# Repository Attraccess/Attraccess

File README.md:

# Attraccess

Attraccess manages machine access and resource usage for industry, R&D and universities. It checks operator permissions and safety briefings, connects machines through PLCs and automation flows, and records usage for reporting and maintenance.

Attraccess runs on your own infrastructure and is **source-available** under the [modified Prosperity Public License 3.0](LICENSE.md). Commercial use requires a license after a 30-day evaluation; qualifying non-commercial use is free under the license terms.

## Features

- Resource Management
  - Track resource status, usage, and maintenance
  - Image support for resources with automatic resizing and caching
  - Operator permissions and documented safety briefings
  - Preventive maintenance scheduling
  - Usage tracking, project attribution and CSV reporting
- Machine Integration
  - Badge access through Attractap readers
  - WAGO PLC integration and automation via MQTT and HTTP
  - Workstation access through Attraccess Companion
- IT & Operations
  - Single sign-on via OIDC and SAML
  - Role-based access control and audit logging
  - On-premises deployment with Prometheus and Grafana monitoring

## Everything below is meant for developers

If you are looking for user documentation, take a look at https://docs.attraccess.org

## Developer Setup

Routine API/frontend work needs:

| Dependency  | Purpose                                              |
| ----------- | ---------------------------------------------------- |
| **Docker**  | `pnpm services` – PostgreSQL, mailpit, authentik, etc. |
| **Node.js** | Exact version pinned in `.nvmrc`                     |
| **pnpm**    | Exact version pinned in `package.json`               |

**Quick setup:**

```bash
./scripts/setup-dev-dependencies.sh
```

This checks the pinned Node and pnpm versions, installs missing host tools, and
sets up the workspace (dependencies, `.env`, submodules, the PostgreSQL database and its migrations).
PostgreSQL is the only supported database. Every checkout gets its own database
`attraccess_<folder>` inside the shared development PostgreSQL
(`pnpm services up postgres`, host port `POSTGRES_PORT`, default 5432); the
bootstrap starts that service when nothing answers, creates the database and writes
`DATABASE_URL` into `.env` (`scripts/setup-dev-database.mjs`).
Host installation is in `scripts/setup-host-dependencies.sh`; workspace setup is
in `scripts/setup-workspace.sh`. To repeat workspace setup without installing
global tools, run `./scripts/setup-dev-dependencies.sh --workspace-only`.
Docker (or any PostgreSQL reachable through `DATABASE_URL` / `DEV_POSTGRES_URL`) is needed for the
development database; services and container tests need a running Docker daemon and the
`docker compose` plugin. Install **Docker** manually if missing:

- **Docker:** `curl -fsSL https://get.docker.com | sh` then `sudo usermod -aG docker $USER` (log out/in)

For Attractap firmware work, also install the project-local ESP-IDF toolchain:

```bash
INSTALL_ESP_IDF=true ./scripts/setup-dev-dependencies.sh --workspace-only
```

## Installation

1. Clone the repository
2. Install dependencies:
   ```bash
   pnpm install
   ```
3. Set up environment variables and the development database (creates `attraccess_<folder>`, writes `DATABASE_URL`):
   ```bash
   cp .env.example .env
   pnpm services up postgres
   node scripts/setup-dev-database.mjs
   ```
4. Run database migrations:
   ```bash
   pnpm nx run api:migrations-run
   ```

## Development

Tooling tests run as an ordinary Nx target, independently of coverage reporting:

```bash
pnpm test:tooling
pnpm nx run api:test-scripts
```

Core CI discovers these targets automatically. `api:test` also runs the seeding
regressions. `pnpm seed:dev -- --demo` creates a local administrator and demo
resources after migrations. Seeding and migrations read `.env`; process variables
take precedence. Both use `DATABASE_URL`; seeding a database on a host other than
localhost requires `--allow-external-db`. API and script tests that need PostgreSQL read
`TEST_DATABASE_URL` (an admin connection such as
`postgres://attraccess:attraccess@127.0.0.1:5432/postgres`) and create one database per test.

Repository checks and generators are available through Nx:

```bash
pnpm lint:files                           # always checks current files
pnpm lint:files --staged                  # always checks the Git index
pnpm nx run @attraccess/source:check-balena-compose
pnpm nx run @attraccess/source:check-brand-assets
pnpm nx run @attraccess/source:generate-brand-assets
```

Validation targets can cache their results. Bootstrap, seeding, migrations,
service management and asset generation always execute.

Start the API and frontend in development mode (HMR), with automatic port resolution:

```bash
pnpm serve
```

By default, startup does not build or copy kiosk (Companion) installers or
Attractap firmware. Build and bundle either set of assets before launching:

```bash
pnpm serve --with-kiosk                  # Companion installers for this host
pnpm serve --with-attractap              # Active Attractap firmware variants
pnpm serve --with-kiosk --with-attractap # Both
```

`--with-companion` is an alias for `--with-kiosk`. These flags also work with
`--only=api`; frontend-only startup cannot prepare API assets. Requested builds
must succeed before the servers launch. Firmware builds require ESP-IDF:
`INSTALL_ESP_IDF=true ./scripts/setup-dev-dependencies.sh`.

CI always tests the deliverables and builds all Companion platforms and active
firmware variants. Docker and Balena consume the same uploaded artifacts;
missing installers or firmware fail the image build.

The launcher probes for free ports and prints them at startup. Defaults:

- API: 3000 (searches 3000–3099)
- Frontend: 4200 (searches 4200–4299)
- Vite preview: 4300 (searches 4300–4399)

Run only one service:

```bash
pnpm serve --only=api
pnpm serve --only=frontend
```

Use the nx interactive terminal UI instead of streamed output (default is streamed, which is agent/CI friendly):

```bash
pnpm serve --tui
```

Pin a specific port (fails loudly if busy):

```bash
PORT=3010 pnpm serve              # API on 3010
VITE_PORT=4250 pnpm serve         # Frontend on 4250
```

The frontend dev proxy automatically targets whichever port the API resolved to (via `VITE_API_PROXY_TARGET`).

The resolved ports are also written to `.dev-serve-ports.json` at the repo root (gitignored, deleted on exit), so you can look them up without reading the banner:

```bash
cat .dev-serve-ports.json
# { "pid": 12345, "api": {...}, "frontend": {...}, "preview": {...} }
```

## API Documentation

Swagger documentation is available at `/api` when the server is running.

## Licensing & Activation

Attraccess includes license verification. Enter your key in the setup wizard or under **Settings → Application Settings**; Attraccess does not read it from environment variables.

- Commercial users: Use the license key you received after purchasing a license.
- Non-profit organizations: You can use Attraccess for free by entering the following special key:

```
I AM USING THIS SOFTWARE ONLY FOR NON-PROFIT AND COMPLY TO ALL TERMS OF THE LICENSE.md at https://github.com/Attraccess/Attraccess/blob/main/LICENSE.md
```

Licensed features require a valid configured key.

Plugins fall under the core license unless they ship their own `LICENSE.md`. The WAGO and Reservations plugins have their own commercial license and need a paid license module (`wago`, `reservations`); the non-profit key does not unlock them.

## Contributing

Please see [CONTRIBUTING.md](CONTRIBUTING.md) for details on our code of conduct and the process for submitting pull requests.

## Lizenz

Dieses Projekt ist **source-available** und steht unter einer modifizierten Version der [Prosperity Public License v3.0](./LICENSE.md).

### ✅ Erlaubt:

- Nutzung, Veränderung und Weitergabe für **Privatpersonen** und **gemeinnützige Organisationen**
- 30-tägige Testnutzung für **kommerzielle Nutzer**

### ❌ Nicht erlaubt:

- Kommerzielle Nutzung über 30 Tage hinaus **ohne kommerzielle Lizenz**
- Verwendung oder Verbreitung von Forks für kommerzielle Zwecke ohne Genehmigung
- Umlizensierung oder Änderung der Lizenzbedingungen

### 🛡️ Schutz vor Fork-Missbrauch

Alle Forks und abgeleiteten Projekte unterliegen denselben Lizenzbedingungen. Kommerzielle Nutzung ist auch in Forks **nicht erlaubt**, es sei denn, es liegt eine gültige Lizenz des ursprünglichen Autors vor.

### 🔌 Plugins

Plugins stehen unter der Lizenz des Kerns, sofern sie keine eigene `LICENSE.md` mitbringen. Die Plugins WAGO und Reservierungen haben eine eigene kommerzielle Lizenz und brauchen ein bezahltes Lizenzmodul (`wago`, `reservations`); der Schlüssel für gemeinnützige Nutzung schaltet sie nicht frei.

### 🔍 MIT-lizenzierte Bestandteile

Dieses Projekt basiert teilweise auf einem MIT-lizenzierten Projekt. Diese Komponenten bleiben unter der MIT-Lizenz verfügbar. Details siehe [LICENSE-fabinfra.md](./LICENSE-fabinfra.md).

---

**Für kommerzielle Nutzung oder Lizenzanfragen:**  
Bitte kontaktiere [contact@attraccess.org](mailto:contact@attraccess.org).

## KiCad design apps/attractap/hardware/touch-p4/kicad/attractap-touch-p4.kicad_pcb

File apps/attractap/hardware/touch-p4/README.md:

# Attractap Touch P4 board

KiCad project, generator, simulations and 3D-printable case of the Attractap Touch P4 reader board
(Nx project `attractap-touch-p4-pcb`). The documentation is in the docs under Hardware:
[docs/en/hardware/touch-p4/overview.md](../../../../docs/en/hardware/touch-p4/overview.md).

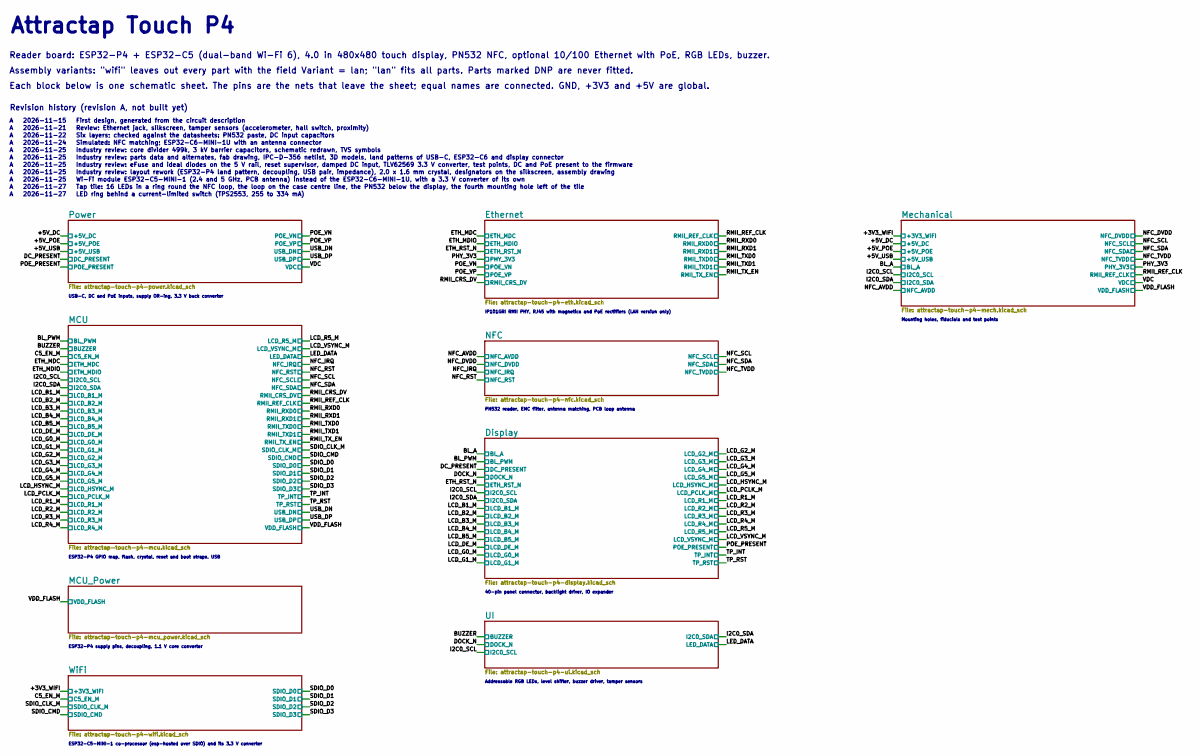
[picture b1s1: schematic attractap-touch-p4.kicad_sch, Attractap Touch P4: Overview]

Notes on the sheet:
USB-C, DC and PoE inputs, supply OR-ing, 3.3 V buck converter
ESP32-P4 GPIO map, flash, crystal, reset and boot straps, USB
ESP32-P4 supply pins, decoupling, 1.1 V core converter
ESP32-C5-MINI-1 co-processor (esp-hosted over SDIO) and its 3.3 V converter
IP101GRI RMII PHY, RJ45 with magnetics and PoE rectifiers (LAN version only)
PN532 reader, EMC filter, antenna matching, PCB loop antenna
40-pin panel connector, backlight driver, IO expander
Addressable RGB LEDs, level shifter, buzzer driver, tamper sensors
Mounting holes, fiducials and test points
Attractap Touch P4
Reader board: ESP32-P4 + ESP32-C5 (dual-band Wi-Fi 6), 4.0 in 480x480 touch display, PN532 NFC, optional 10/100 Ethernet with PoE, RGB LEDs, buzzer.
Assembly variants: "wifi" leaves out every part with the field Variant = lan; "lan" fits all parts. Parts marked DNP are never fitted.
Each block below is one schematic sheet. The pins are the nets that leave the sheet; equal names are connected. GND, +3V3 and +5V are global.
Revision history (revision A, not built yet)
A 2026-11-15 First design, generated from the circuit description
A 2026-11-21 Review: Ethernet jack, silkscreen, tamper sensors (accelerometer, hall switch, proximity)
A 2026-11-22 Six layers; checked against the datasheets: PN532 paste, DC input capacitors
A 2026-11-24 Simulated: NFC matching; ESP32-C6-MINI-1U with an antenna connector
A 2026-11-25 Industry review: core divider 499k, 3 kV barrier capacitors, schematic redrawn, TVS symbols
A 2026-11-25 Industry review: parts data and alternates, fab drawing, IPC-D-356 netlist, 3D models, land patterns of USB-C, ESP32-C6 and display connector
A 2026-11-25 Industry review: eFuse and ideal diodes on the 5 V rail, reset supervisor, damped DC input, TLV62569 3.3 V converter, test points, DC and PoE present to the firmware
A 2026-11-25 Industry review: layout rework (ESP32-P4 land pattern, decoupling, USB pair, impedance), 2.0 x 1.6 mm crystal, designators on the silkscreen, assembly drawing
A 2026-11-25 Wi-Fi module ESP32-C5-MINI-1 (2.4 and 5 GHz, PCB antenna) instead of the ESP32-C6-MINI-1U, with a 3.3 V converter of its own
A 2026-11-27 Tap tile: 16 LEDs in a ring round the NFC loop, the loop on the case centre line, the PN532 below the display, the fourth mounting hole left of the tile
A 2026-11-27 LED ring behind a current-limited switch (TPS2553, 255 to 334 mA)

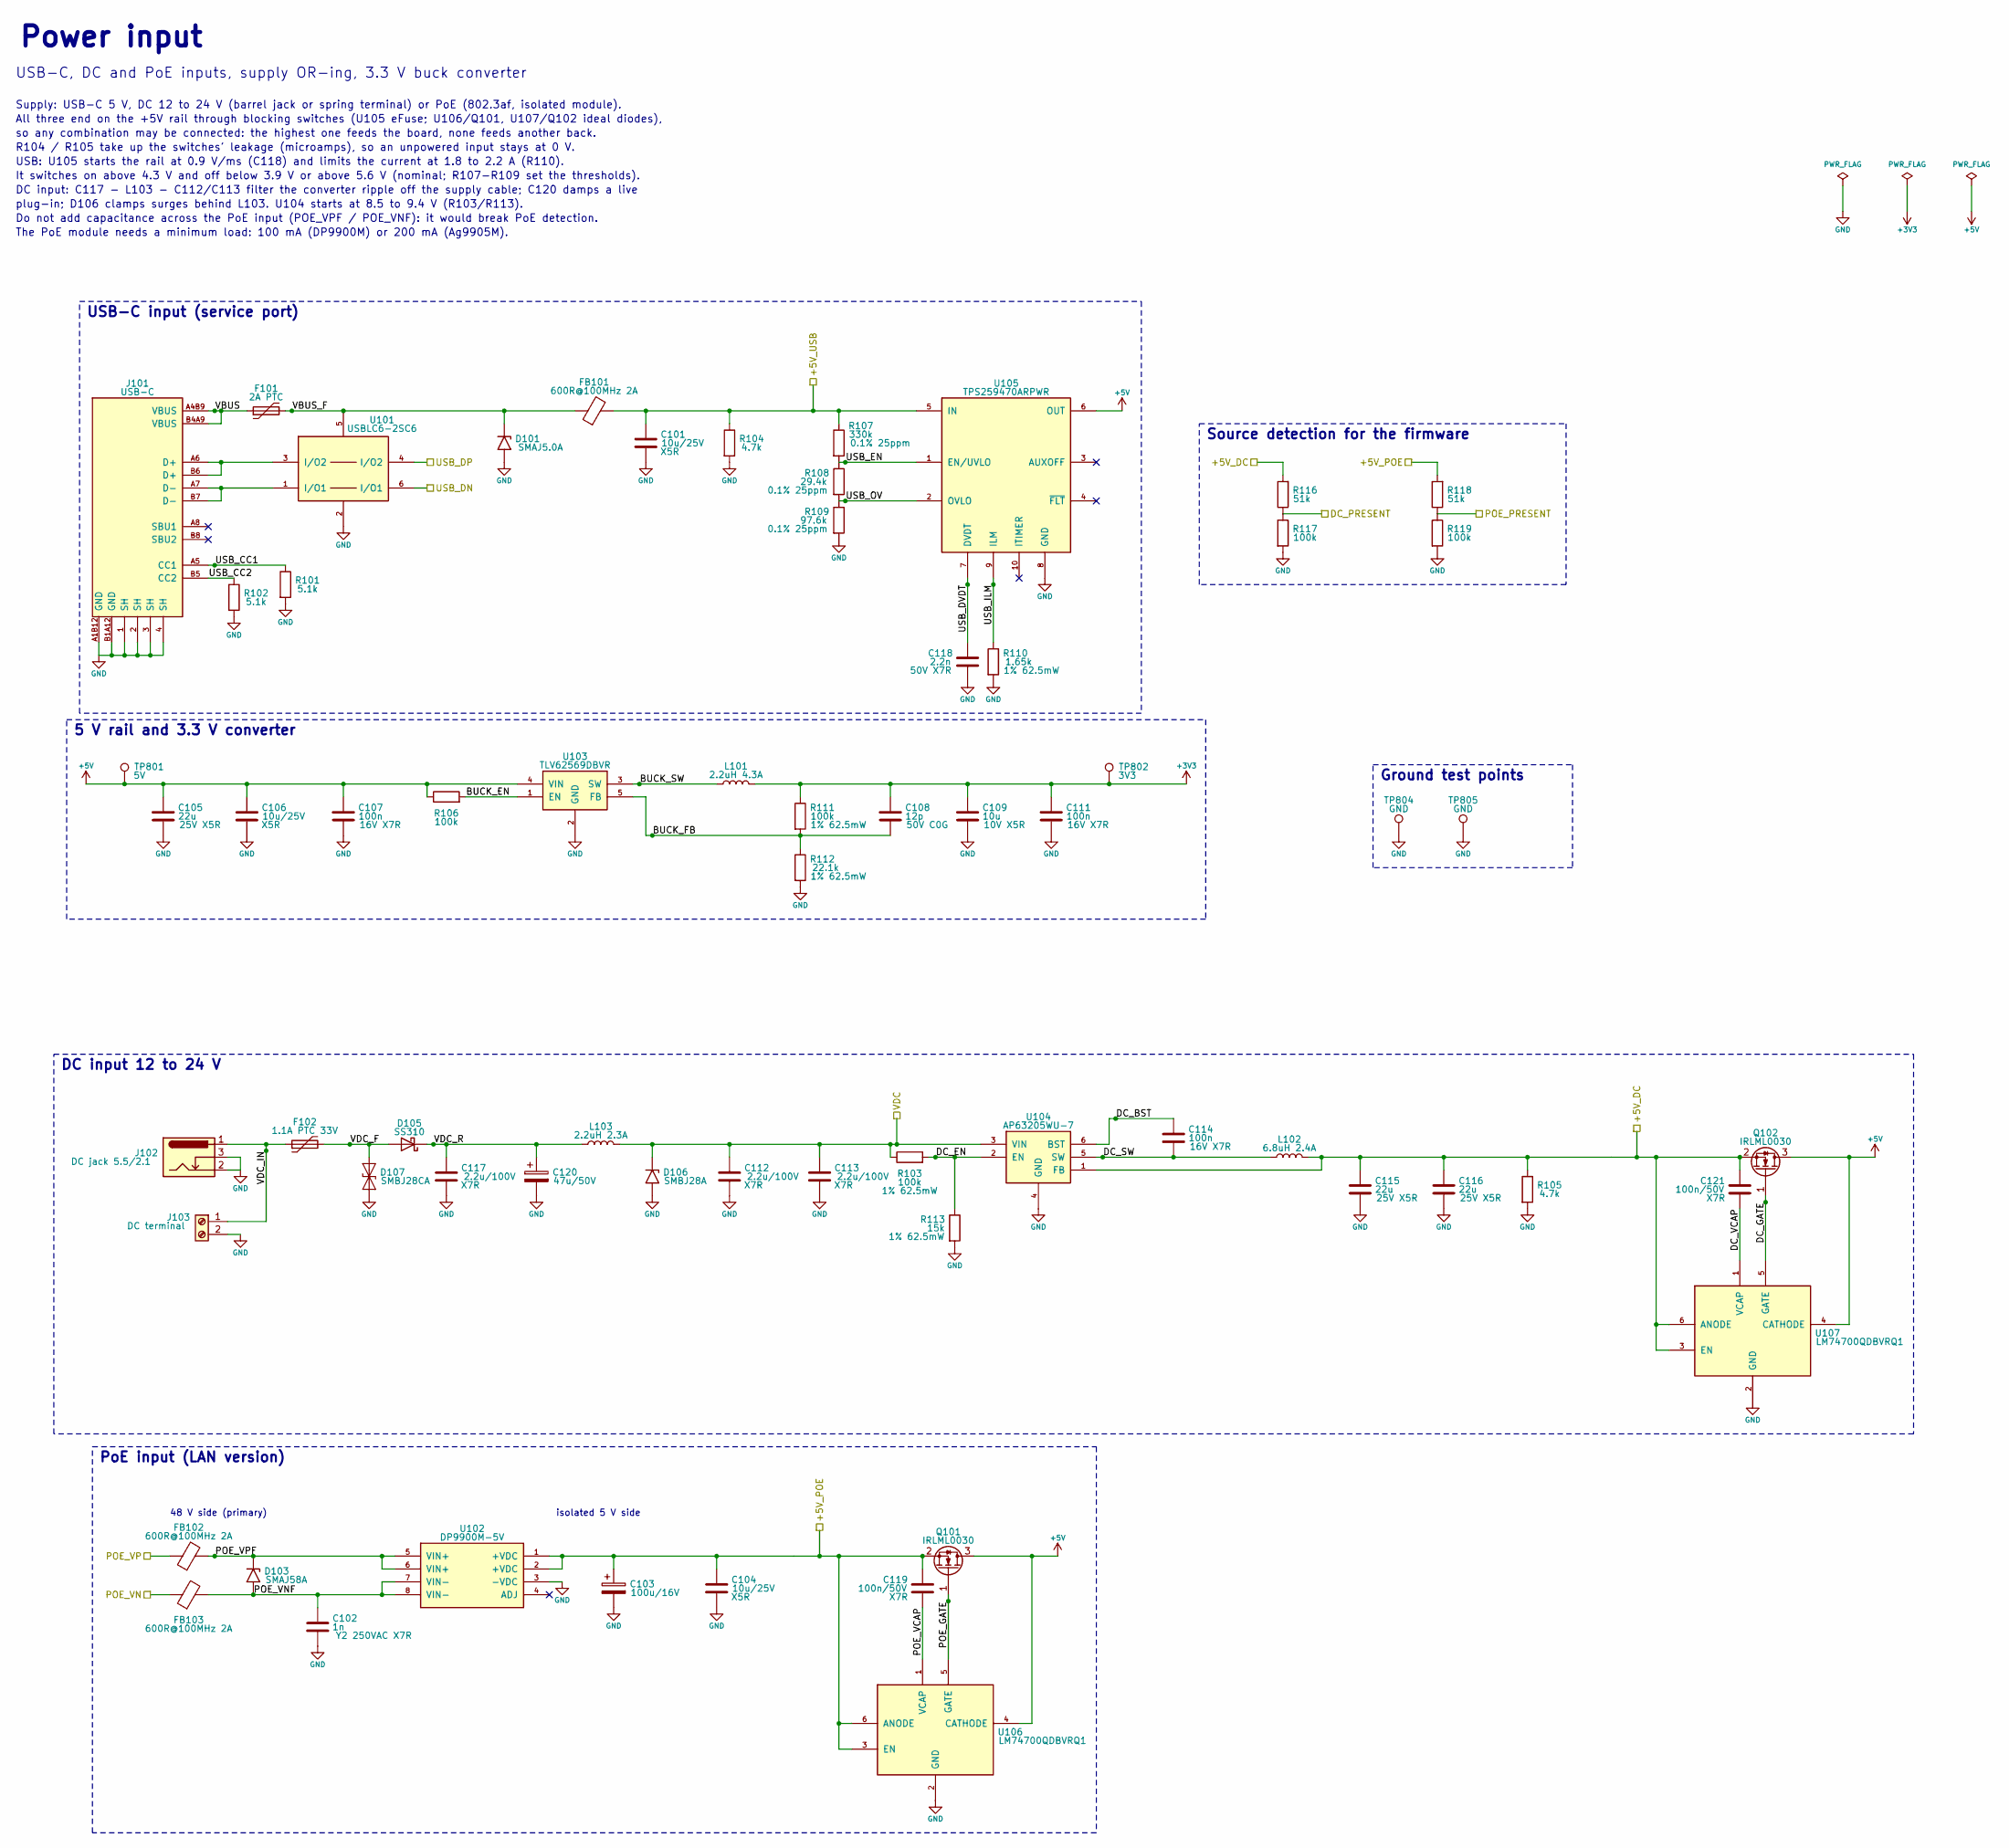
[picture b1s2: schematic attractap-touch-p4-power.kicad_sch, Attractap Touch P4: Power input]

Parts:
C101, C104, C106: 10u/25V; C_0805_2012Metric; Rating X5R; MPN CL21A106KAYNNNE; LCSC C15850
C102: 1n; C_2211_5728Metric_Y2; Rating Y2 250VAC X7R; MPN GA352QR7GF102KW01L; LCSC C91599
C103: 100u/16V; CP_Elec_6.3x5.4; MPN FVH016ADA101M0654; LCSC C7469977
C105, C115, C116: 22u; C_0805_2012Metric; Rating 25V X5R; MPN CL21A226MAQNNNE; LCSC C45783
C107, C111, C114: 100n; C_0402_1005Metric; Rating 16V X7R; MPN CL05B104KO5NNNC; LCSC C1525
C108: 12p; C_0402_1005Metric; Rating 50V C0G; MPN 0402CG120J500NT; LCSC C1547
C109: 10u; C_0603_1608Metric; Rating 10V X5R; MPN CL10A106KP8NNNC; LCSC C19702
C112, C113, C117: 2.2u/100V; C_1206_3216Metric; Rating X7R; MPN CL31B225KCHSNNE; LCSC C170101
C118: 2.2n; C_0402_1005Metric; Rating 50V X7R; MPN CL05B222KB5NNNC; LCSC C84703
C119, C121: 100n/50V; C_0402_1005Metric; Rating X7R; MPN CL05B104KB54PNC; LCSC C307331
C120: 47u/50V; CP_Elec_6.3x7.7; MPN UCD1H470MCL1GS; LCSC C251040
D101: SMAJ5.0A; SMA_L4.3-W2.6-LS5.2-RD; MPN SMAJ5.0A; LCSC C19077523
D103: SMAJ58A; SMA_L4.3-W2.6-LS5.2-RD; MPN SMAJ58A; LCSC C19077554
D105: SS310; SMA_L4.3-W2.6-LS5.2-RD; MPN SS310; LCSC C7420364
D106: SMBJ28A; D_SMB; MPN SMBJ28A; LCSC C178227
D107: SMBJ28CA; D_SMB; MPN SMBJ28CA; LCSC C151259
F101: 2A PTC; F1812; MPN MF-MSMF200L-2; LCSC C89650
F102: 1.1A PTC 33V; F1812; MPN SMD1812P110TF/33; LCSC C21000
FB101, FB102, FB103: 600R@100MHz 2A; L0805; MPN MPZ2012S601AT000; LCSC C21519
J101: USB-C; USB-C_SMD-TYPE-C-31-M-12_1; MPN TYPE-C-31-M-12; LCSC C165948
J102: DC jack 5.5/2.1; DC-IN-TH_PJ-002A; MPN PJ-002A; LCSC C3096082
J103: DC terminal; CONN-TH_4P-P3.5-2601-3102; MPN 250-202; LCSC C2765061
L101: 2.2uH 4.3A; IND-SMD_L4.0-W4.0; MPN WPN4020H2R2MT; LCSC C98361
L102: 6.8uH 2.4A; IND-SMD_L4.0-W4.0; MPN CKCSA4020-6.8uH/M; LCSC C5291940
L103: 2.2uH 2.3A; IND-SMD_L2.5-W2.0_CKCSA252012; MPN CKCSA252012-2.2uH/M; LCSC C354540
Q101, Q102: IRLML0030; SOT-23; MPN IRLML0030TRPBF; LCSC C67272
R101, R102: 5.1k; R_0402_1005Metric; Rating 1% 62.5mW; MPN 0402WGF5101TCE; LCSC C25905
R103, R106, R111, R117, R119: 100k; R_0402_1005Metric; Rating 1% 62.5mW; MPN 0402WGF1003TCE; LCSC C25741
R104, R105: 4.7k; R_0402_1005Metric; Rating 1% 62.5mW; MPN 0402WGF4701TCE; LCSC C25900
R107: 330k; R_0603_1608Metric; Rating 0.1% 25ppm; MPN RT0603BRD07330KL; LCSC C861327
R108: 29.4k; R_0402_1005Metric; Rating 0.1% 25ppm; MPN RT0402BRD0729K4L; LCSC C852690
R109: 97.6k; R_0402_1005Metric; Rating 0.1% 25ppm; MPN RT0402BRD0797K6L; LCSC C852964
R110: 1.65k; R_0402_1005Metric; Rating 1% 62.5mW; MPN 0402WGF1651TCE; LCSC C25869
R112: 22.1k; R_0402_1005Metric; Rating 1% 62.5mW; MPN 0402WGF2212TCE; LCSC C43473
R113: 15k; R_0402_1005Metric; Rating 1% 62.5mW; MPN 0402WGF1502TCE; LCSC C25756
R116, R118: 51k; R_0402_1005Metric; Rating 1% 62.5mW; MPN 0402WGF5102TCE; LCSC C25794
TP801: 5V; TestPoint_Pad_D1.5mm
TP802: 3V3; TestPoint_Pad_D1.5mm
TP804, TP805: GND; TestPoint_Pad_D1.5mm
U101: USBLC6-2SC6; SOT-23-6_L2.9-W1.6-P0.95-LS2.8-BL; MPN USBLC6-2SC6; LCSC C7519
U102: DP9900M-5V; PWRM-SMD_DP9900M-5V; MPN DP9900M-5V; LCSC C5380106
U103: TLV62569DBVR; SOT-23-5_L3.0-W1.7-P0.95-LS2.8-BR; MPN TLV62569DBVR; LCSC C141836
U104: AP63205WU-7; TSOT-26_L2.9-W1.6-P0.95-LS2.8-BL; MPN AP63205WU-7; LCSC C2071056
U105: TPS259470ARPWR; VQFN-10_L2.0-W2.0-P0.45-TL; MPN TPS259470ARPWR; LCSC C3662799
U106, U107: LM74700QDBVRQ1; SOT-23-6_L2.9-W1.6-P0.95-LS2.8-BL; MPN LM74700QDBVRQ1; LCSC C2941042

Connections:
+3V3: C108.1, C109.1, C111.1, L101.2, R111.1, TP802.1; also elsewhere on the board
+5V: C105.1, C106.1, C107.1, Q101.3 (D), Q102.3 (D), R106.1, TP801.1, U103.4 (VIN), U105.6 (OUT), U106.4 (CATHODE), U107.4 (CATHODE); also elsewhere on the board
/+5V_DC: C115.1, C116.1, C121.1, L102.2, Q102.2 (S), R105.1, R116.2, U104.1 (FB), U107.3 (EN), U107.6 (ANODE); also elsewhere on the board
/+5V_POE: C103.1, C104.1, C119.1, Q101.2 (S), R118.2, U102.1 (+VDC), U102.2 (+VDC), U106.3 (EN), U106.6 (ANODE); also elsewhere on the board
/+5V_USB: C101.1, FB101.2, R104.1, R107.1, U105.5 (IN); also elsewhere on the board
/DC_PRESENT: R116.1, R117.1; also elsewhere on the board
/POE_PRESENT: R118.1, R119.1; also elsewhere on the board
/POE_VN: FB103.1; also elsewhere on the board
/POE_VP: FB102.1; also elsewhere on the board
/Power/BUCK_EN: R106.2, U103.1 (EN)
/Power/BUCK_FB: C108.2, R111.2, R112.1, U103.5 (FB)
/Power/BUCK_SW: L101.1, U103.3 (SW)
/Power/DC_BST: C114.1, U104.6 (BST)
/Power/DC_EN: R103.2, R113.1, U104.2 (EN)
/Power/DC_GATE: Q102.1 (G), U107.5 (GATE)
/Power/DC_SW: C114.2, L102.1, U104.5 (SW)
/Power/DC_VCAP: C121.2, U107.1 (VCAP)
/Power/POE_GATE: Q101.1 (G), U106.5 (GATE)
/Power/POE_VCAP: C119.2, U106.1 (VCAP)
/Power/POE_VNF: C102.1, D103.2 (A2), FB103.2, U102.7 (VIN-), U102.8 (VIN-)
/Power/POE_VPF: D103.1 (A1), FB102.2, U102.5 (VIN+), U102.6 (VIN+)
/Power/USB_CC1: J101.A5 (CC1), R101.1
/Power/USB_CC2: J101.B5 (CC2), R102.1
/Power/USB_DVDT: C118.1, U105.7 (DVDT)
/Power/USB_EN: R107.2, R108.1, U105.1 (EN/UVLO)
/Power/USB_ILM: R110.1, U105.9 (ILM)
/Power/USB_OV: R108.2, R109.1, U105.2 (OVLO)
/Power/VBUS: F101.1, J101.A4B9 (VBUS), J101.B4A9 (VBUS)
/Power/VBUS_F: D101.1 (A1), F101.2, FB101.1, U101.5
/Power/VDC_F: D105.2 (A), D107.1 (A1), F102.2
/Power/VDC_IN: F102.1, J102.1, J103.1
/Power/VDC_R: C117.1, C120.1, D105.1 (K), L103.1
/VDC: C112.1, C113.1, D106.1 (K), L103.2, R103.1, U104.3 (VIN); also elsewhere on the board
GND: C101.2, C102.2, C103.2, C104.2, C105.2, C106.2, C107.2, C109.2, C111.2, C112.2, C113.2, C115.2, C116.2, C117.2, C118.2, C120.2, D101.2 (A2), D106.2 (A), D107.2 (A2), J101.1 (SH), J101.2 (SH), J101.3 (SH), J101.4 (SH), J101.A1B12 (GND), J101.B1A12 (GND), J102.2, J102.3, J103.2, R101.2, R102.2, R104.2, R105.2, R109.2, R110.2, R112.2, R113.2, R117.2, R119.2, TP804.1, TP805.1, U101.2, U102.3 (-VDC), U103.2 (GND), U104.4 (GND), U105.8 (GND), U106.2 (GND), U107.2 (GND); also elsewhere on the board

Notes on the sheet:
Power input
USB-C, DC and PoE inputs, supply OR-ing, 3.3 V buck converter
Supply: USB-C 5 V, DC 12 to 24 V (barrel jack or spring terminal) or PoE (802.3af, isolated module).
All three end on the +5V rail through blocking switches (U105 eFuse; U106/Q101, U107/Q102 ideal diodes),
so any combination may be connected: the highest one feeds the board, none feeds another back.
R104 / R105 take up the switches' leakage (microamps), so an unpowered input stays at 0 V.
USB: U105 starts the rail at 0.9 V/ms (C118) and limits the current at 1.8 to 2.2 A (R110).
It switches on above 4.3 V and off below 3.9 V or above 5.6 V (nominal; R107-R109 set the thresholds).
DC input: C117 - L103 - C112/C113 filter the converter ripple off the supply cable; C120 damps a live
plug-in; D106 clamps surges behind L103. U104 starts at 8.5 to 9.4 V (R103/R113).
Do not add capacitance across the PoE input (POE_VPF / POE_VNF): it would break PoE detection.
The PoE module needs a minimum load: 100 mA (DP9900M) or 200 mA (Ag9905M).
48 V side (primary)
isolated 5 V side
USB-C input (service port)
Source detection for the firmware
5 V rail and 3.3 V converter
DC input 12 to 24 V
PoE input (LAN version)
Ground test points

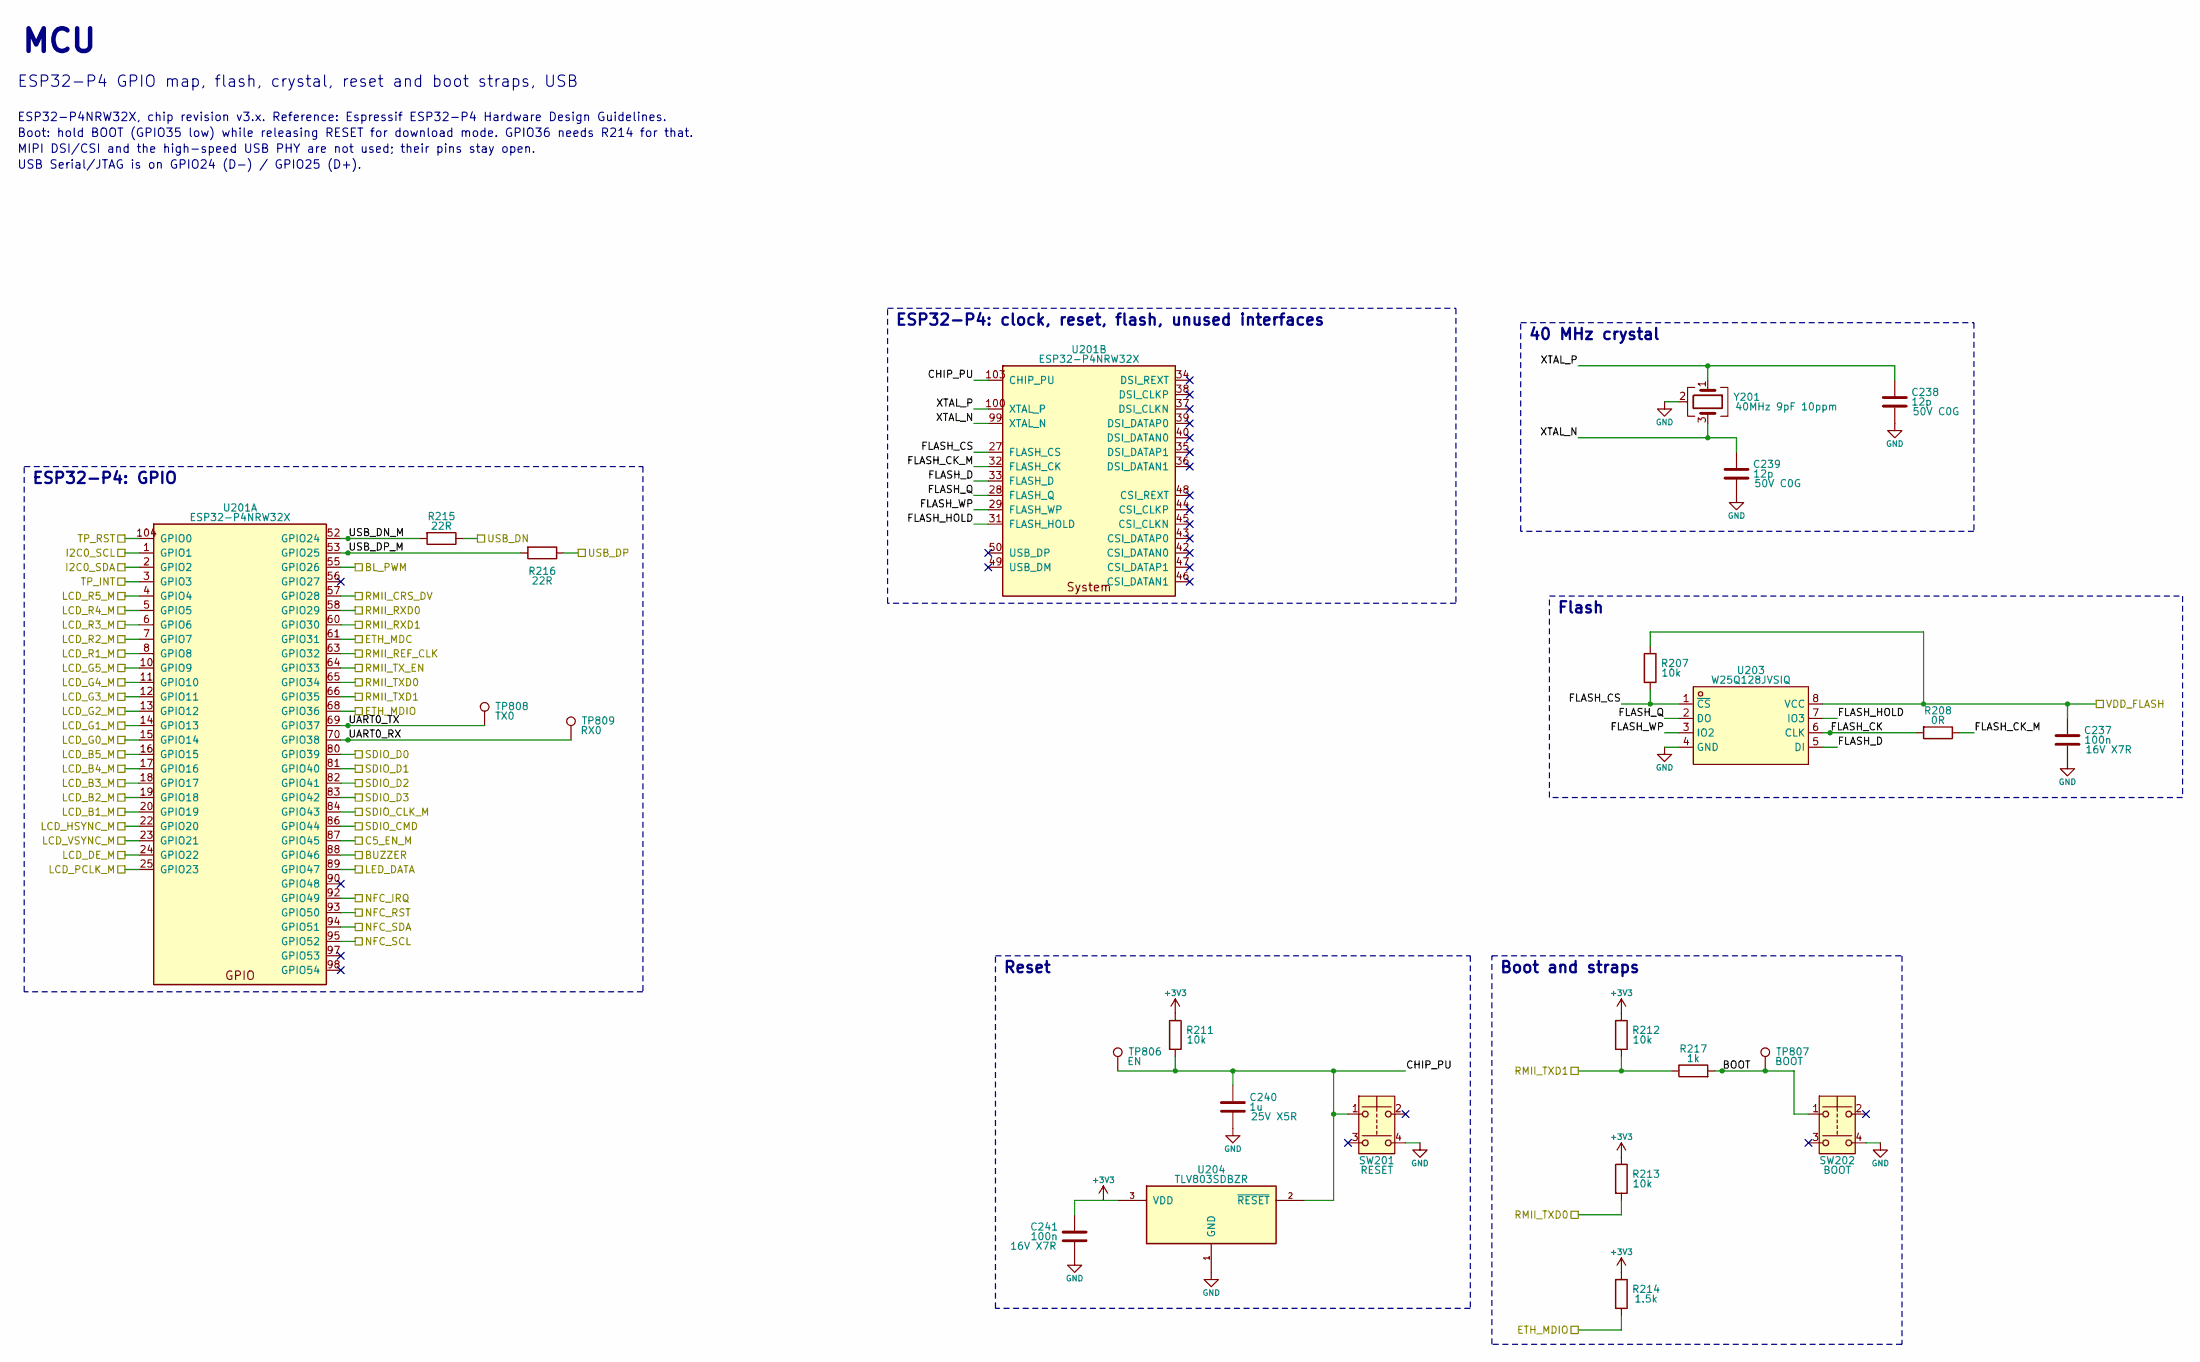
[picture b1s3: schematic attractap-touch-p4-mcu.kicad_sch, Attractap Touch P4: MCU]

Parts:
C237, C241: 100n; C_0402_1005Metric; Rating 16V X7R; MPN CL05B104KO5NNNC; LCSC C1525
C238, C239: 12p; C_0402_1005Metric; Rating 50V C0G; MPN 0402CG120J500NT; LCSC C1547
C240: 1u; C_0402_1005Metric; Rating 25V X5R; MPN CL05A105KA5NQNC; LCSC C52923
R207, R211, R212, R213: 10k; R_0402_1005Metric; Rating 1% 62.5mW; MPN 0402WGF1002TCE; LCSC C25744
R208: 0R; R_0402_1005Metric; Rating jumper 62.5mW; MPN 0402WGF0000TCE; LCSC C17168
R214: 1.5k; R_0402_1005Metric; Rating 1% 62.5mW; MPN 0402WGF1501TCE; LCSC C25867
R215, R216: 22R; R_0402_1005Metric; Rating 1% 62.5mW; MPN 0402WGF220JTCE; LCSC C25092
R217: 1k; R_0402_1005Metric; Rating 1% 62.5mW; MPN 0402WGF1001TCE; LCSC C11702
SW201: RESET; SW-SMD_4P-L5.1-W5.1-P3.70-LS6.5-TL_H1.5; MPN TS-1187A-B-A-B; LCSC C318884
SW202: BOOT; SW-SMD_4P-L5.1-W5.1-P3.70-LS6.5-TL_H1.5; MPN TS-1187A-B-A-B; LCSC C318884
TP806: EN; TestPoint_Pad_D1.5mm
TP807: BOOT; TestPoint_Pad_D1.5mm
TP808: TX0; TestPoint_Pad_D1.5mm
TP809: RX0; TestPoint_Pad_D1.5mm
U201: ESP32-P4NRW32X; QFN-104_L10.0-W10.0-P0.35-TL-EP7.5; MPN ESP32-P4NRW32X; LCSC C54540373
U203: W25Q128JVSIQ; SOIC-8_L5.3-W5.3-P1.27-LS8.0-BL; MPN W25Q128JVSIQ; LCSC C97521
U204: TLV803SDBZR; SOT-23; MPN TLV803SDBZR; LCSC C132016
Y201: 40MHz 9pF 10ppm; Crystal_SMD_2016-4Pin_2.0x1.6mm; MPN E1SB40E00001AE; LCSC C2689435

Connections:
+3V3: C241.1, R211.1, R212.1, R213.1, R214.1, U204.3 (VDD); also elsewhere on the board
/BL_PWM: U201.55 (GPIO26); also elsewhere on the board
/BUZZER: U201.88 (GPIO46); also elsewhere on the board
/C5_EN_M: U201.87 (GPIO45); also elsewhere on the board
/ETH_MDC: U201.61 (GPIO31); also elsewhere on the board
/ETH_MDIO: R214.2, U201.68 (GPIO36); also elsewhere on the board
/I2C0_SCL: U201.1 (GPIO1); also elsewhere on the board
/I2C0_SDA: U201.2 (GPIO2); also elsewhere on the board
/LCD_B1_M: U201.20 (GPIO19); also elsewhere on the board
/LCD_B2_M: U201.19 (GPIO18); also elsewhere on the board
/LCD_B3_M: U201.18 (GPIO17); also elsewhere on the board
/LCD_B4_M: U201.17 (GPIO16); also elsewhere on the board
/LCD_B5_M: U201.16 (GPIO15); also elsewhere on the board
/LCD_DE_M: U201.24 (GPIO22); also elsewhere on the board
/LCD_G0_M: U201.15 (GPIO14); also elsewhere on the board
/LCD_G1_M: U201.14 (GPIO13); also elsewhere on the board
/LCD_G2_M: U201.13 (GPIO12); also elsewhere on the board
/LCD_G3_M: U201.12 (GPIO11); also elsewhere on the board
/LCD_G4_M: U201.11 (GPIO10); also elsewhere on the board
/LCD_G5_M: U201.10 (GPIO9); also elsewhere on the board
/LCD_HSYNC_M: U201.22 (GPIO20); also elsewhere on the board
/LCD_PCLK_M: U201.25 (GPIO23); also elsewhere on the board
/LCD_R1_M: U201.8 (GPIO8); also elsewhere on the board
/LCD_R2_M: U201.7 (GPIO7); also elsewhere on the board
/LCD_R3_M: U201.6 (GPIO6); also elsewhere on the board
/LCD_R4_M: U201.5 (GPIO5); also elsewhere on the board
/LCD_R5_M: U201.4 (GPIO4); also elsewhere on the board
/LCD_VSYNC_M: U201.23 (GPIO21); also elsewhere on the board
/LED_DATA: U201.89 (GPIO47); also elsewhere on the board
/MCU/BOOT: R217.2, SW202.1, TP807.1
/MCU/CHIP_PU: C240.1, R211.2, SW201.1, TP806.1, U201.103 (CHIP_PU), U204.2 (~RESET)
/MCU/FLASH_CK: R208.2, U203.6 (CLK)
/MCU/FLASH_CK_M: R208.1, U201.32 (FLASH_CK)
/MCU/FLASH_CS: R207.2, U201.27 (FLASH_CS), U203.1 (~CS)
/MCU/FLASH_D: U201.33 (FLASH_D), U203.5 (DI)
/MCU/FLASH_HOLD: U201.31 (FLASH_HOLD), U203.7 (IO3)
/MCU/FLASH_Q: U201.28 (FLASH_Q), U203.2 (DO)
/MCU/FLASH_WP: U201.29 (FLASH_WP), U203.3 (IO2)
/MCU/UART0_RX: TP809.1, U201.70 (GPIO38)
/MCU/UART0_TX: TP808.1, U201.69 (GPIO37)
/MCU/USB_DN_M: R215.2, U201.52 (GPIO24)
/MCU/USB_DP_M: R216.2, U201.53 (GPIO25)
/MCU/XTAL_N: C239.1, U201.99 (XTAL_N), Y201.3
/MCU/XTAL_P: C238.1, U201.100 (XTAL_P), Y201.1
/NFC_IRQ: U201.92 (GPIO49); also elsewhere on the board
/NFC_RST: U201.93 (GPIO50); also elsewhere on the board
/NFC_SCL: U201.95 (GPIO52); also elsewhere on the board
/NFC_SDA: U201.94 (GPIO51); also elsewhere on the board
/RMII_CRS_DV: U201.57 (GPIO28); also elsewhere on the board
/RMII_REF_CLK: U201.63 (GPIO32); also elsewhere on the board
/RMII_RXD0: U201.58 (GPIO29); also elsewhere on the board
/RMII_RXD1: U201.60 (GPIO30); also elsewhere on the board
/RMII_TXD0: R213.2, U201.65 (GPIO34); also elsewhere on the board
/RMII_TXD1: R212.2, R217.1, U201.66 (GPIO35); also elsewhere on the board
/RMII_TX_EN: U201.64 (GPIO33); also elsewhere on the board
/SDIO_CLK_M: U201.84 (GPIO43); also elsewhere on the board
/SDIO_CMD: U201.86 (GPIO44); also elsewhere on the board
/SDIO_D0: U201.80 (GPIO39); also elsewhere on the board
/SDIO_D1: U201.81 (GPIO40); also elsewhere on the board
/SDIO_D2: U201.82 (GPIO41); also elsewhere on the board
/SDIO_D3: U201.83 (GPIO42); also elsewhere on the board
/TP_INT: U201.3 (GPIO3); also elsewhere on the board
/TP_RST: U201.104 (GPIO0); also elsewhere on the board
/VDD_FLASH: C237.1, R207.1, U203.8 (VCC); also elsewhere on the board
GND: C237.2, C238.2, C239.2, C240.2, C241.2, SW201.4, SW202.4, U203.4 (GND), U204.1 (GND), Y201.2 (G), Y201.4 (G); also elsewhere on the board

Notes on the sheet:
MCU
ESP32-P4 GPIO map, flash, crystal, reset and boot straps, USB
ESP32-P4NRW32X, chip revision v3.x. Reference: Espressif ESP32-P4 Hardware Design Guidelines.
Boot: hold BOOT (GPIO35 low) while releasing RESET for download mode. GPIO36 needs R214 for that.
MIPI DSI/CSI and the high-speed USB PHY are not used; their pins stay open.
USB Serial/JTAG is on GPIO24 (D-) / GPIO25 (D+).
ESP32-P4: GPIO
ESP32-P4: clock, reset, flash, unused interfaces
40 MHz crystal
Flash
Reset
Boot and straps
